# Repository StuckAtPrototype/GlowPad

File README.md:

# GlowPad

A multi-mode interactive pad built on the ESP32-S3 with 5 capacitive touch keys, 5 WS2812B LEDs, and a piezo buzzer. Supports five modes: a Pomodoro timer, a pentatonic piano, a Simon-style memory game, a reaction speed game, and a USB media-control (keyboard) mode for music players.

## Hardware

| Peripheral | Details |
|---|---|
| MCU | ESP32-S3-WROOM-1 |
| Touch inputs | 5 capacitive pads (CAP1-CAP5) on GPIO 4, 5, 3, 2, 1 |
| LEDs | 5x IN-PI15TAT5R5G5B (WS2812B) chain on GPIO 21 (via BSS138 level shifter) |
| Buzzer | Piezo (SMT1240SHT) on GPIO 48 (via transistor driver) |
| USB | Native USB-C (D+/D− on GPIO 20/19) for HID + programming |
| Power | AP2205 3.3V LDO |

### PCB / Design Files

The board is designed in [KiCad](https://www.kicad.org/) (v8+). Design sources and
manufacturing outputs live under `hardware/GlowPad/`:

| File / Folder | Contents |
|---|---|
| `GlowPad.kicad_pro` | KiCad project file |
| `GlowPad.kicad_sch` | Schematic |
| `GlowPad.kicad_pcb` | PCB layout |
| `GlowPad_BOM.csv` | Bill of materials |
| `gerber/` | Gerber + drill files for fabrication |

To open the design, launch KiCad and open `hardware/GlowPad/GlowPad.kicad_pro`.

#### Key components (see `GlowPad_BOM.csv` for the full BOM)

| Ref | Part | Function |
|---|---|---|
| U1 | ESP32-S3-WROOM-1 | MCU |
| U6 | AP2205-33 | 3.3V LDO regulator |
| Q1 | BSS138 | LED data level shifter |
| D5 | TPD1E10B06 | USB ESD protection |
| J1 | USB4105-GF-A | USB-C connector |
| LED1-5 | IN-PI15TAT5R5G5B | Addressable RGB LEDs |
| TCH1-5 | Capacitive pads | Touch keys |
| LS1 | SMT1240SHT | Piezo buzzer |
| SW1 / SW2 | RKB2 tactile | Reset / Boot (enable) |

## Modes

Switch modes by long-pressing keys 1–5 (pads 1–5).

### 1. Pomodoro Timer (key 1 long press)

A focus timer with five preset durations mapped to the five keys:

| Key | Duration |
|---|---|
| 1 | 5 min |
| 2 | 10 min |
| 3 | 25 min |
| 4 | 45 min |
| 5 | 60 min |

LEDs show a green progress bar while running. After the timer completes, a 60-second grace period starts (pulsing green). If not dismissed, it enters a 60-second alert with pulsing red LEDs and an audible jingle.

**Idle LEDs:** cyan at 30%.

### 2. Piano (key 2 long press)

Each key plays a note from the C-major pentatonic scale:

| Key | Note | Frequency |
|---|---|---|
| 1 | C5 | 523 Hz |
| 2 | D5 | 587 Hz |
| 3 | E5 | 659 Hz |
| 4 | G5 | 784 Hz |
| 5 | A5 | 880 Hz |

The corresponding LED flashes its colour at full brightness while the note plays, then fades back to a dim rainbow idle pattern.

**Idle LEDs:** rainbow (red, yellow, green, cyan, blue) at 20%.

### 3. Memory Game (key 3 long press)

A Simon-style memory game. The system plays an ever-growing random sequence of lights and tones. The player must repeat the sequence by pressing the matching keys in order.

- Each round adds one element to the sequence
- Correct presses flash the key's colour and play its tone
- Wrong press or 3-second timeout ends the game
- Score (rounds completed) is displayed on the LEDs at game over

**Idle LEDs:** yellow at 30%.

### 4. Reaction Game (key 4 long press)

A speed-and-accuracy reaction test over 5 rounds.

1. A random LED lights up after a random delay (0.5-1.5 seconds)
2. Press the matching key as fast as possible
3. Pressing before the LED appears counts as a false start (no penalty, round restarts)
4. After 5 rounds, the score is displayed as 0-5 green LEDs (one per "good" round)

A "good" round requires pressing the correct key in under 450ms. Per-round times and the total time are printed to the serial console.

**Idle LEDs:** purple at 30%.

### 5. Media Control (key 5 long press)

USB HID Consumer (media keys) mode. Connect GlowPad to the host via **native USB** (ESP32-S3 USB D+/D− on GPIO 20/19). The five pads act as media keys:

| Key | Action |
|---|---|
| 1 | Previous track |
| 2 | Play / Pause |
| 3 | Next track |
| 4 | Volume down |
| 5 | Volume up |

Works with most music players (Spotify, VLC, system media keys, etc.). Short press sends the key; the corresponding LED flashes for feedback.

**Idle LEDs:** orange/amber at 30%.

**Note:** Media mode requires the `esp_tinyusb` component (pulled in automatically) and HID enabled in menuconfig (`CONFIG_TINYUSB_HID_ENABLED`). The firmware uses a custom HID Consumer report descriptor.

## Building

Requires [ESP-IDF v5.5+](https://docs.espressif.com/projects/esp-idf/en/stable/esp32s3/get-started/).

```bash
cd GlowPad/firmware
idf.py set-target esp32s3
idf.py build
idf.py -p COMx flash monitor
```

## Project Structure

```
GlowPad/
├── firmware/                # ESP-IDF application
│   └── main/
│       ├── main.c              # Entry point, initialises peripherals and main loop
│       ├── mode_manager.c/h    # Mode switching and dispatch
│       ├── button.c/h          # Capacitive touch driver (ESP32-S3 touch sensor v2)
│       ├── led.c/h             # High-level LED control (progress bar, pulsing, per-LED colour)
│       ├── ws2812_control.c/h  # Low-level WS2812 RMT driver
│       ├── piezo.c/h           # Piezo buzzer driver (LEDC PWM)
│       ├── timer.c/h           # Pomodoro timer state machine
│       ├── piano.c/h           # Piano mode
│       ├── memory_game.c/h     # Simon-style memory game
│       ├── reaction_game.c/h   # Reaction speed game
│       ├── media_control.c/h   # USB HID media keys mode
│       ├── led_color_lib.c/h   # Colour generation utilities
│       └── serial_protocol.c/h # Serial protocol (placeholder)
└── hardware/
    └── GlowPad/             # KiCad project (schematic, PCB, BOM, gerbers)
```

## License

See [LICENSE](LICENSE).

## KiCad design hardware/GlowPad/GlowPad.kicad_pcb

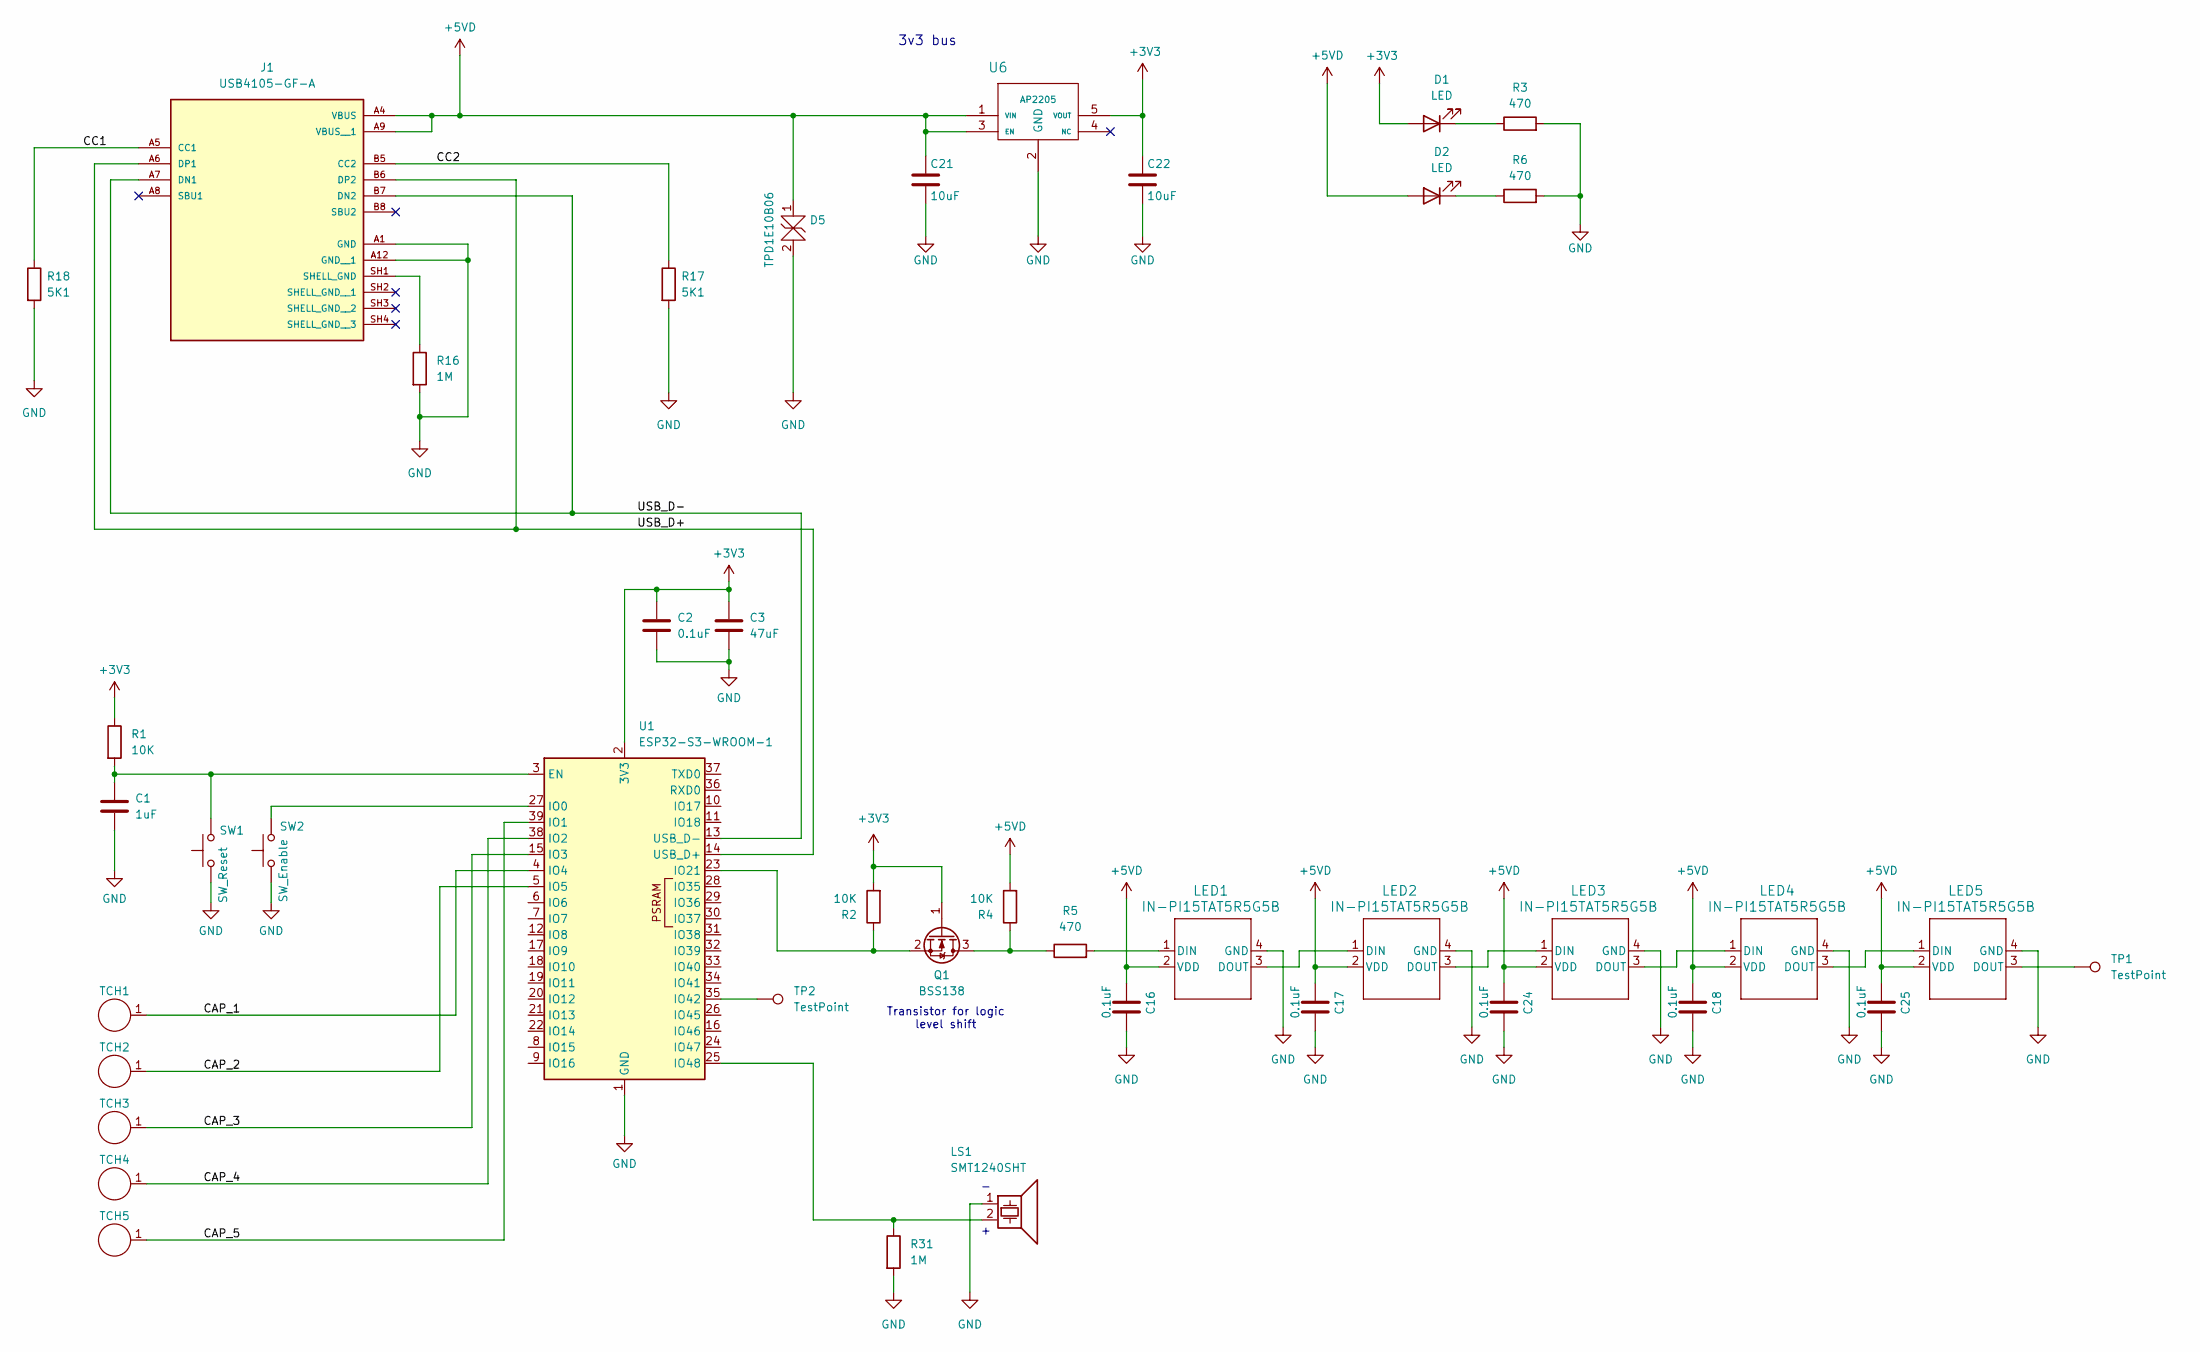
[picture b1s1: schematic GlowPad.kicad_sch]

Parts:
C1: 1uF; C_0603_1608Metric
C2, C16, C17, C18, C24, C25: 0.1uF; C_0603_1608Metric
C3: 47uF; C_0603_1608Metric
C21, C22: 10uF; C_0603_1608Metric
D1, D2: LED; LED_0603_1608Metric
D5: TPD1E10B06; D_SOD-523
J1: USB4105-GF-A; GCT_USB4105-GF-A; PARTREV B4
LED1, LED2, LED3, LED4, LED5: IN-PI15TAT5R5G5B; IN-PI15_INL
LS1: SMT1240SHT
Q1: BSS138; SOT-23
R1, R2, R4: 10K; R_0603_1608Metric
R3, R5, R6: 470; R_0603_1608Metric
R16, R31: 1M; R_0603_1608Metric
R17, R18: 5K1; R_0603_1608Metric
SW1: SW_Reset; SWITCH_0SMTRLFS
SW2: SW_Enable; SWITCH_0SMTRLFS
TCH1, TCH2, TCH3, TCH4, TCH5: CapButton_18_26
TP1, TP2: TestPoint; TestPoint_Pad_2.0x2.0mm
U1: ESP32-S3-WROOM-1
U6: AP2205; AP2204

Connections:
+3V3: C2.1, C3.1, C22.1, D1.2 (A), Q1.1 (G), R1.1, R2.2, U1.2 (3V3), U6.5 (VOUT)
+5VD: C16.1, C17.1, C18.1, C21.1, C24.1, C25.1, D2.2 (A), D5.1, J1.A4 (VBUS), J1.A9 (VBUS__1), LED1.2 (VDD), LED2.2 (VDD), LED3.2 (VDD), LED4.2 (VDD), LED5.2 (VDD), R4.2, U6.1 (VIN), U6.3 (EN)
/CAP_1: TCH1.1, U1.4 (IO4)
/CAP_2: TCH2.1, U1.5 (IO5)
/CAP_3: TCH3.1, U1.15 (IO3)
/CAP_4: TCH4.1, U1.38 (IO2)
/CAP_5: TCH5.1, U1.39 (IO1)
/CC1: J1.A5 (CC1), R18.1
/CC2: J1.B5 (CC2), R17.1
/USB_D+: J1.A6 (DP1), J1.B6 (DP2), U1.14 (USB_D+)
/USB_D-: J1.A7 (DN1), J1.B7 (DN2), U1.13 (USB_D-)
GND: C1.2, C2.2, C3.2, C16.2, C17.2, C18.2, C21.2, C22.2, C24.2, C25.2, D5.2, J1.A1 (GND), J1.A12 (GND__1), LED1.4 (GND), LED2.4 (GND), LED3.4 (GND), LED4.4 (GND), LED5.4 (GND), LS1.1, R3.2, R6.2, R16.2, R17.2, R18.2, R31.2, SW1.1, SW2.1, U1.1 (GND), U1.40 (GND), U1.41 (GND), U6.2 (GND)
unnamed: D1.1 (K), R3.1
unnamed: D2.1 (K), R6.1
unnamed: J1.SH1 (SHELL_GND), R16.1
unnamed: LED1.1 (DIN), R5.2
unnamed: LED1.3 (DOUT), LED2.1 (DIN)
unnamed: LED2.3 (DOUT), LED3.1 (DIN)
unnamed: LED3.3 (DOUT), LED4.1 (DIN)
unnamed: LED4.3 (DOUT), LED5.1 (DIN)
unnamed: LED5.3 (DOUT), TP1.1
unnamed: Q1.3 (D), R4.1, R5.1
unnamed: Q1.2 (S), R2.1, U1.23 (IO21)
unnamed: C1.1, R1.2, SW1.2, U1.3 (EN)
unnamed: SW2.2, U1.27 (IO0)
unnamed: TP2.1, U1.35 (IO42)
unnamed: LS1.2, R31.1, U1.25 (IO48)

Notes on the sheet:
Transistor for logic level shift
3v3 bus

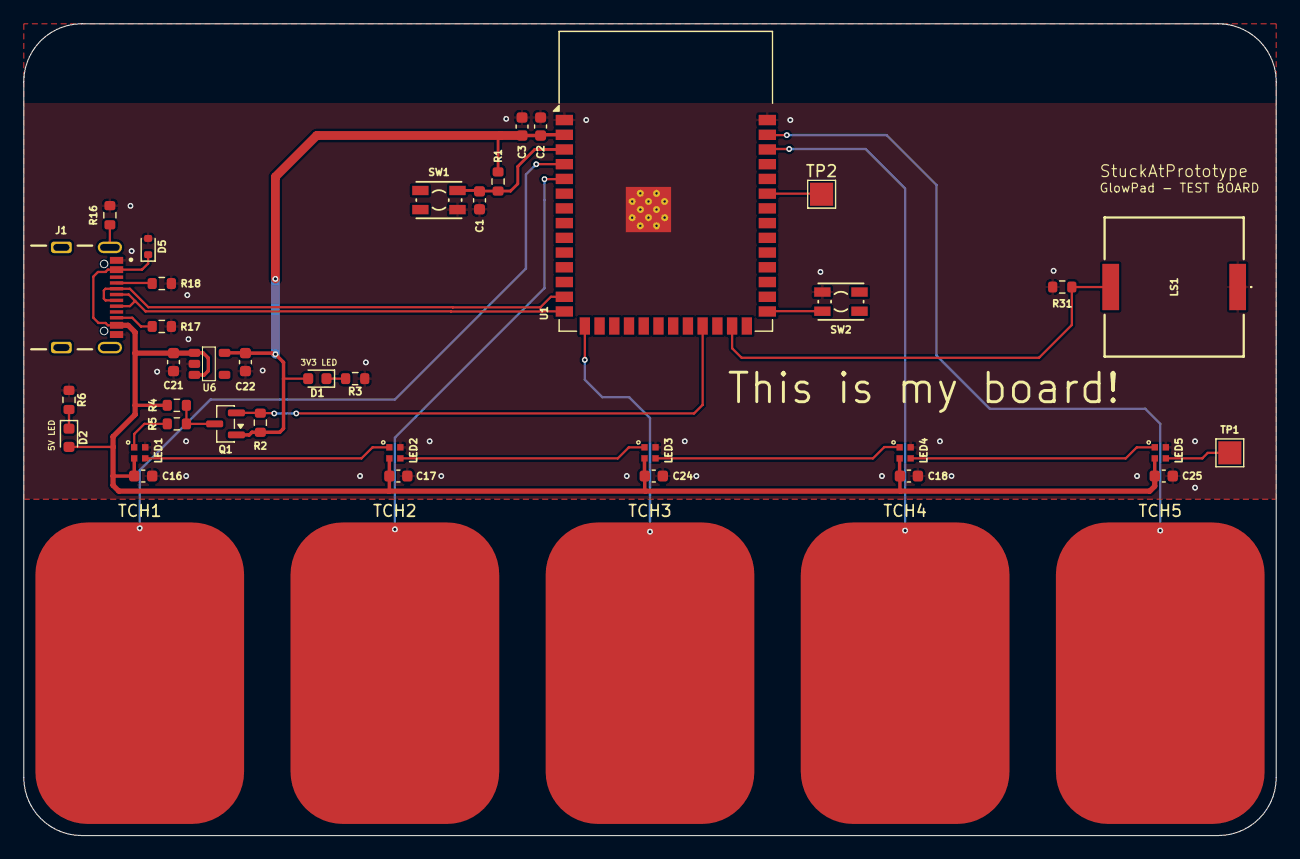
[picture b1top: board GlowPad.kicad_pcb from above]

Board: 2 copper layers, 108.0 x 70.0 mm, 42 parts (0 on the bottom side), 27 nets.

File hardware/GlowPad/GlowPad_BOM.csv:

Id,Designator,Footprint,Quantity,Designation,Supplier and ref
1,"C18,C16,C2,C24,C25,C17",C_0603_1608Metric,6,0.1uF,CC0603KRX7R7BB104
2,U1,ESP32-S3-WROOM-1,1,ESP32-S3-WROOM-1,ESP32-S3-WROOM-1
3,D5,D_SOD-523,1,TPD1E10B06,TPD1E10B06DYAR
4,TP1,TestPoint_Pad_2.0x2.0mm,1,TestPoint,DNP
5,"R3,R6,R5",R_0603_1608Metric,3,470,ESR03EZPF4700
6,C1,C_0603_1608Metric,1,1uF,CC0603KRX5R8BB105
7,"C21,C22",C_0603_1608Metric,2,10uF,GRM188R61A106ME69D
8,"R4,R2,R1",R_0603_1608Metric,3,10K,WR06X103 JTL
9,J1,GCT_USB4105-GF-A,1,USB4105-GF-A,USB4105-GF-A
10,"R17,R18",R_0603_1608Metric,2,5K1,RC0603FR-075K1L
11,"D1,D2",LED_0603_1608Metric,2,LED,DNP
12,"TCH1,TCH2,TCH4,TCH5,TCH3",CapButton_18_26,5,~,DNP
13,"LED5,LED4,LED3,LED2,LED1",IN-PI15_INL,5,IN-PI15TAT5R5G5B,IN-PI15TAT5R5G5B
14,"R16,R31",R_0603_1608Metric,2,1M,RMCF0603FT1M00
15,U6,AP2204,1,AP2205,AP2205-33W5-7
16,SW1,SWITCH_0SMTRLFS,1,SW_Reset,RKB2SJK250SMTR LFS
17,SW2,SWITCH_0SMTRLFS,1,SW_Enable,RKB2SJK250SMTR LFS
18,Q1,SOT-23,1,BSS138,BSS138
19,C3,C_0603_1608Metric,1,47uF,GRM188C80E476ME05D
20,LS1,SMT1240SHT,1,SMT1240SHT,SMT1240SHT

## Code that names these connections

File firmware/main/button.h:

/**
 * @file button.h
 * @brief Capacitive touch button interface for Pomodoro timer
 * 
 * Provides the same public API as the original GPIO-button driver,
 * but uses ESP32-S3 capacitive touch pads for input.
 * 
 * @author StuckAtPrototype, LLC
 * @version 3.0
 */

#ifndef BUTTON_H
#define BUTTON_H

#include <stdint.h>
#include <stdbool.h>

#ifdef __cplusplus
extern "C" {
#endif

// Touch pad channel IDs (ESP32-S3 touch sensor v2)
#define TOUCH_CAP1_CHAN  4   // GPIO4 / TOUCH_PAD_NUM4 - CAP_1
#define TOUCH_CAP2_CHAN  5   // GPIO5 / TOUCH_PAD_NUM5 - CAP_2
#define TOUCH_CAP3_CHAN  3   // GPIO3 / TOUCH_PAD_NUM3 - CAP_3
#define TOUCH_CAP4_CHAN  2   // GPIO2 / TOUCH_PAD_NUM2 - CAP_4
#define TOUCH_CAP5_CHAN  1   // GPIO1 / TOUCH_PAD_NUM1 - CAP_5

// Button indices (unchanged from original)
#define BUTTON_SW0 0
#define BUTTON_SW1 1
#define BUTTON_SW2 2
#define BUTTON_SW3 3
#define BUTTON_SW4 4
#define NUM_BUTTONS 5

// Button press types
typedef enum {
    BUTTON_PRESS_SHORT = 0,
    BUTTON_PRESS_LONG = 1
} button_press_type_t;

// Button event callback type
typedef void (*button_event_callback_t)(uint8_t button_id, button_press_type_t press_type);

/**
 * @brief Initialize capacitive touch button system
 * 
 * Configures ESP32-S3 touch sensor controller and 5 touch channels,
 * performs initial calibration, and starts continuous scanning.
 */
void button_init(void);

/**
 * @brief Register a callback for button events
 * 
 * @param callback Function to call when a button event occurs
 */
void button_register_callback(button_event_callback_t callback);

#ifdef __cplusplus
}
#endif

#endif // BUTTON_H

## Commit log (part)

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2026-03-02 initial working version with just pomodoro
2026-03-02 adding a piano mode
2026-03-03 adding a memory game
2026-03-03 adding a reaction game
2026-03-03 adding a readme
2026-03-04 fix gitignore for firmware build outputs
    Made-with: Cursor
2026-03-09 working GlowPad with 5 different modes
